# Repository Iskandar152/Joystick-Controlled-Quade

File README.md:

# Joystick-Controlled-Quade

## Project Goal

Creating a quadraped robot that uses an ultra sonic sensor and joystick to allow wireless control. The information from the ultra sonic sensor will allow the controller to guide the robot even if the controller cannot see where it is.

## MSP432 UART Connection

Based off [TI UART example code](http://dev.ti.com/tirex/explore/node?node=AHgBmlbzFK.HTw3HuKF7Cw__z-lQYNj__LATEST)
This example was chosen as the base because the baud rate was already set at 9600 which is necessary for communication with the Arduino Uno.

Altered to allow communication over the 3.2 and 3.3 pins on the MSP432 so that it can be connected to and Arduino Uno. It works with a receive interrupt that will then transmit the information from the ultra sonic sensor. 

## Arduino Blynk Code

Based off examples from the Blynk library, [Joystick Example](https://examples.blynk.cc/?board=Arduino%20Uno&shield=ESP8266%20WiFi%20Shield&example=Widgets%2FJoystickTwoAxis) and [Virtual Display](https://examples.blynk.cc/?board=Arduino%20Uno&shield=ESP8266%20WiFi%20Shield&example=GettingStarted%2FVirtualPinWrite).
Our code combines these examples and alters the display so that it is comstantly updating whenever new data is available.

This was an easy way to have a wireless connection with the MSP432 that just needed the addition of the UART communication to work with the TX and RX pins. The code creates an array for the joystick inputs and writes the sensor values to a digital display.

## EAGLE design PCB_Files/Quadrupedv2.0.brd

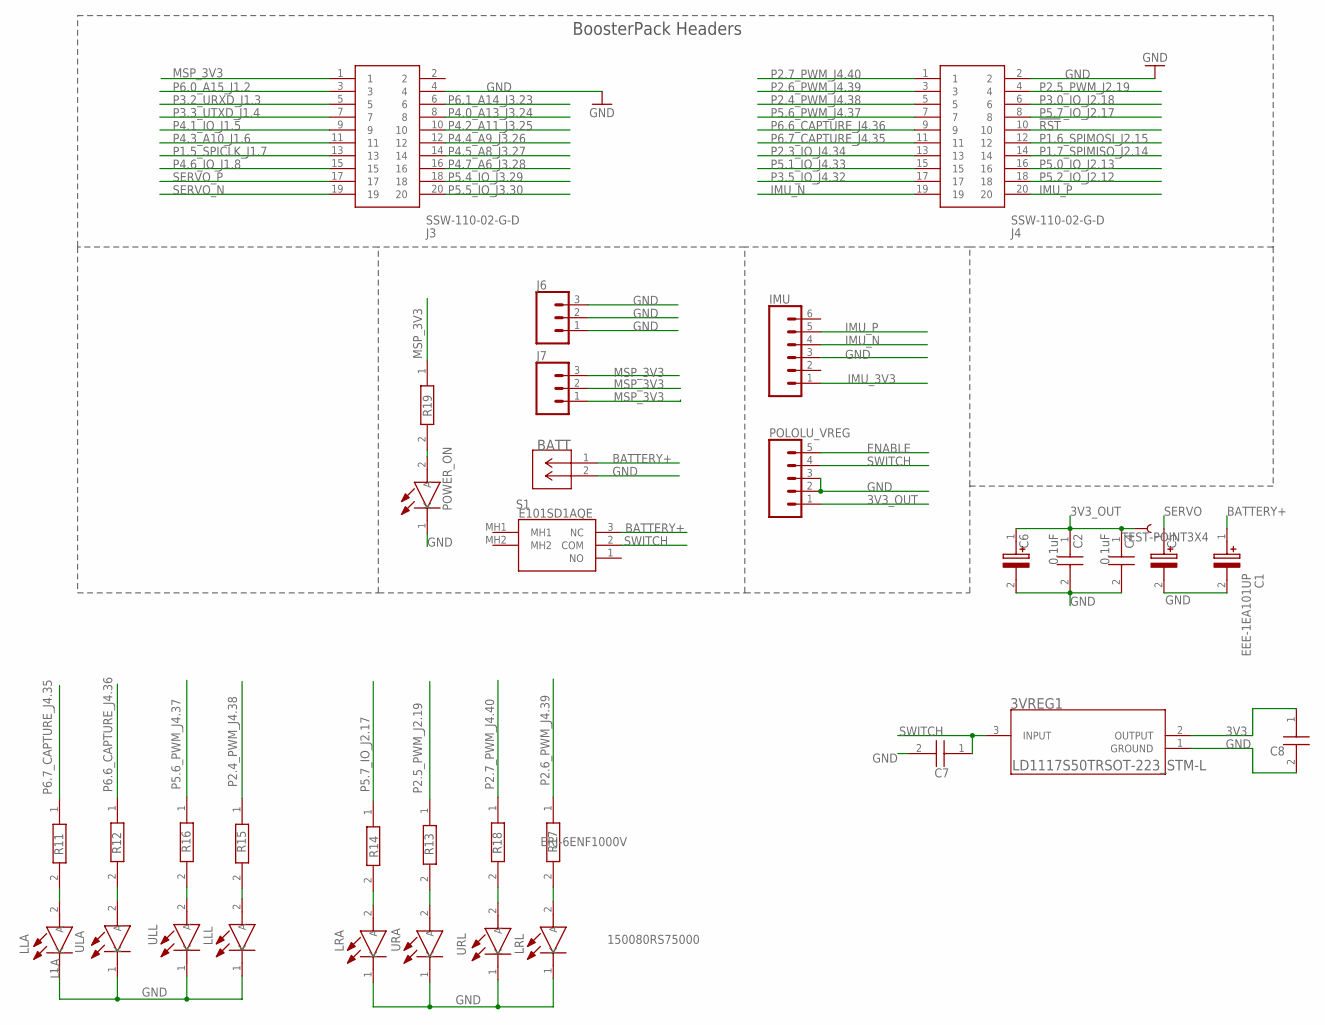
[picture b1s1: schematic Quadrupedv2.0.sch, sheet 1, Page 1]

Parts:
3VREG1: LD1117S50TRSOT-223_STM-L; SOT-223_STM-L
BATT: 640456-2; CONN2_640456-2_TEC
C1, C5, C6: EEE-1EA101UP; CAPAE830X650N
C2, C4: 0.1uF; CAPC2012X88N
C7, C8: C0805C104K5RAC7411; CAPC2012X88N
IMU: CONN_06SILK_FEMALE_PTH; 1X06
J3, J4: SSW-110-02-G-D; SAMTEC_SSW-110-02-G
J6, J7: CONN_03CONN_3F; 1X03_FEMALE
LLA: 150080RS75000; LEDC2012X80N
LLL: 150080RS75000; LEDC2012X80N
LRA: 150080RS75000; LEDC2012X80N
LRL: 150080RS75000; LEDC2012X80N
POLOLU_VREG: CONN_05; 1X05
POWER_ON: 150080RS75000; LEDC2012X80N
R11, R12, R13, R14, R15, R16, R17, R18, R19: ERJ-6ENF1000V; RESC2012X70N
S1: E101SD1AQE
TP22: TEST-POINT3X4; PAD.03X.04
ULA: 150080RS75000; LEDC2012X80N
ULL: 150080RS75000; LEDC2012X80N
URA: 150080RS75000; LEDC2012X80N
URL: 150080RS75000; LEDC2012X80N

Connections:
3V3: 3VREG1.2 (OUTPUT), C8.1; also elsewhere on the board
3V3_OUT: C2.1, C4.1, C6.1 (+), POLOLU_VREG.1, TP22.P$1; also elsewhere on the board
!RST: J4.10
BATTERY+: BATT.1, C1.1 (+), S1.3 (NC)
ENABLE: POLOLU_VREG.5
GND: 3VREG1.1 (GROUND), BATT.2, C1.2 (-), C2.2, C4.2, C5.2 (-), C6.2 (-), C7.2, C8.2, IMU.3, J3.4, J4.2, J6.1, J6.2, J6.3, LLA.1 (K), LLL.1 (K), LRA.1 (K), LRL.1 (K), POLOLU_VREG.2, POLOLU_VREG.3, POWER_ON.1 (K), ULA.1 (K), ULL.1 (K), URA.1 (K), URL.1 (K); also elsewhere on the board
IMU_3V3: IMU.1; also elsewhere on the board
IMU_N: IMU.4, J4.19
IMU_P: IMU.5, J4.20
MSP_3V3: J3.1, J7.1, J7.2, J7.3, R19.1; also elsewhere on the board
unnamed: R12.2, ULA.2 (A)
unnamed: LLA.2 (A), R11.2
unnamed: R16.2, ULL.2 (A)
unnamed: LLL.2 (A), R15.2
unnamed: R13.2, URA.2 (A)
unnamed: LRA.2 (A), R14.2
unnamed: R18.2, URL.2 (A)
unnamed: LRL.2 (A), R17.2
unnamed: POWER_ON.2 (A), R19.2
P1.5_SPICLK_J1.7: J3.13
P1.6_SPIMOSI_J2.15: J4.12
P1.7_SPIMISO_J2.14: J4.14
P2.3_IO_J4.34: J4.13
P2.4_PWM_J4.38: J4.5, R15.1
P2.5_PWM_J2.19: J4.4, R13.1
P2.6_PWM_J4.39: J4.3, R17.1
P2.7_PWM_J4.40: J4.1, R18.1
P3.0_IO_J2.18: J4.6
P3.2_URXD_J1.3: J3.5
P3.3_UTXD_J1.4: J3.7
P3.5_IO_J4.32: J4.17
P4.0_A13_J3.24: J3.8
P4.1_IO_J1.5: J3.9
P4.2_A11_J3.25: J3.10
P4.3_A10_J1.6: J3.11
P4.4_A9_J3.26: J3.12
P4.5_A8_J3.27: J3.14
P4.6_IO_J1.8: J3.15
P4.7_A6_J3.28: J3.16
P5.0_IO_J2.13: J4.16
P5.1_IO_J4.33: J4.15
P5.2_IO_J2.12: J4.18
P5.4_IO_J3.29: J3.18
P5.5_IO_J3.30: J3.20
P5.6_PWM_J4.37: J4.7, R16.1
P5.7_IO_J2.17: J4.8, R14.1
P6.0_A15_J1.2: J3.3
P6.1_A14_J3.23: J3.6
P6.6_CAPTURE_J4.36: J4.9, R12.1
P6.7_CAPTURE_J4.35: J4.11, R11.1
SERVO: C5.1 (+); also elsewhere on the board
SERVO_N: J3.19; also elsewhere on the board
SERVO_P: J3.17; also elsewhere on the board
SWITCH: 3VREG1.3 (INPUT), C7.1, POLOLU_VREG.4, S1.2 (COM)

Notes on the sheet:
BoosterPack Headers

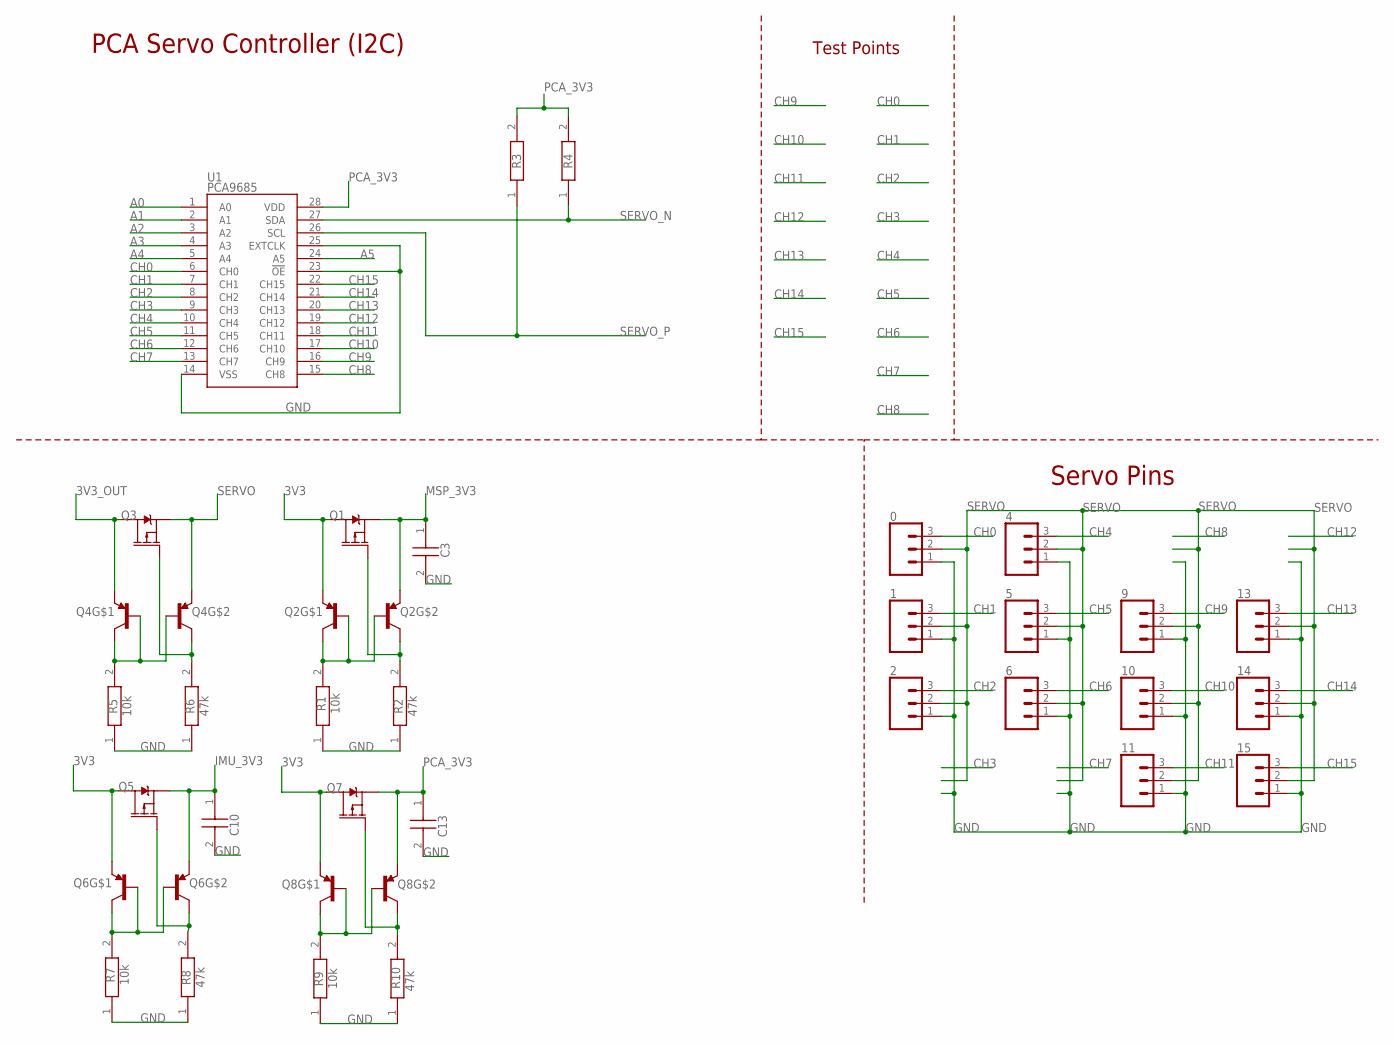
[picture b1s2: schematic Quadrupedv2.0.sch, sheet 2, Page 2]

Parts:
0, 1, 2, 4, 5, 6, 9, 10, 11, 13, 14, 15: CONN_03; 1X03MALE
C3, C10, C13: C0805C104K5RAC7411; CAPC2012X88N
Q1, Q3, Q5, Q7: 2.5A/30V/105mΩ; SOT23-3
Q2, Q4, Q6, Q8: TRANS_PNP_DUALSOT-363; SOT363_PHILIPS
R1, R5, R7, R9: 10k; RESC2012X70N
R2, R6, R8, R10: 47k; RESC2012X70N
R3, R4: ERJ-6ENF1000V; RESC2012X70N
U1: PCA9685; TSSOP-28_4MM

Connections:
3V3: Q1.3 (D), Q2.1 (E), Q5.3 (D), Q6.1 (E), Q7.3 (D), Q8.1 (E); also elsewhere on the board
3V3_OUT: Q3.3 (D), Q4.1 (E); also elsewhere on the board
A0: U1.1 (A0)
A1: U1.2 (A1)
A2: U1.3 (A2)
A3: U1.4 (A3)
A4: U1.5 (A4)
A5: U1.24 (A5)
CH0: 0.3, U1.6 (CH0)
CH1: 1.3, U1.7 (CH1)
CH2: 2.3, U1.8 (CH2)
CH3: U1.9 (CH3)
CH4: 4.3, U1.10 (CH4)
CH5: 5.3, U1.11 (CH5)
CH6: 6.3, U1.12 (CH6)
CH7: U1.13 (CH7)
CH8: U1.15 (CH8)
CH9: 9.3, U1.16 (CH9)
CH10: 10.3, U1.17 (CH10)
CH11: 11.3, U1.18 (CH11)
CH12: U1.19 (CH12)
CH13: 13.3, U1.20 (CH13)
CH14: 14.3, U1.21 (CH14)
CH15: 15.3, U1.22 (CH15)
GND: 0.1, 1.1, 2.1, 4.1, 5.1, 6.1, 9.1, 10.1, 11.1, 13.1, 14.1, 15.1, C3.2, C10.2, C13.2, R1.1, R2.1, R5.1, R6.1, R7.1, R8.1, R9.1, R10.1, U1.14 (VSS), U1.23 (!OE), U1.25 (EXTCLK); also elsewhere on the board
IMU_3V3: C10.1, Q5.2 (S), Q6.4 (E); also elsewhere on the board
MSP_3V3: C3.1, Q1.2 (S), Q2.4 (E); also elsewhere on the board
unnamed: Q7.1 (G), Q8.3 (C), R10.2
unnamed: Q8.2 (B), Q8.5 (B), Q8.6 (C), R9.2
unnamed: Q1.1 (G), Q2.3 (C), R2.2
unnamed: Q2.2 (B), Q2.5 (B), Q2.6 (C), R1.2
unnamed: Q5.1 (G), Q6.3 (C), R8.2
unnamed: Q6.2 (B), Q6.5 (B), Q6.6 (C), R7.2
unnamed: Q4.2 (B), Q4.5 (B), Q4.6 (C), R5.2
unnamed: Q3.1 (G), Q4.3 (C), R6.2
PCA_3V3: C13.1, Q7.2 (S), Q8.4 (E), R3.2, R4.2, U1.28 (VDD)
SERVO: 0.2, 1.2, 2.2, 4.2, 5.2, 6.2, 9.2, 10.2, 11.2, 13.2, 14.2, 15.2, Q3.2 (S), Q4.4 (E); also elsewhere on the board
SERVO_N: R4.1, U1.27 (SDA); also elsewhere on the board
SERVO_P: R3.1, U1.26 (SCL); also elsewhere on the board

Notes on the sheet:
PCA Servo Controller (I2C)
Test Points
Servo Pins

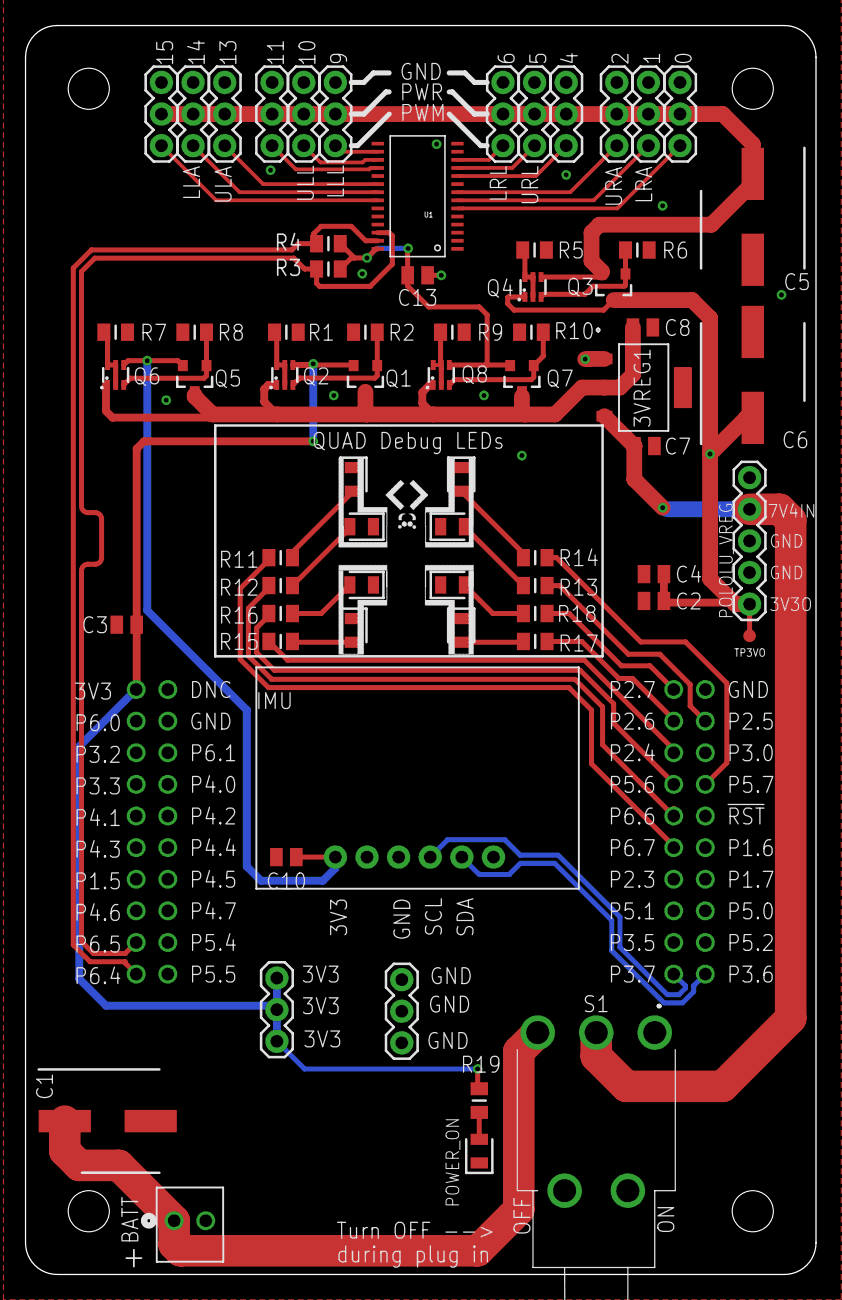
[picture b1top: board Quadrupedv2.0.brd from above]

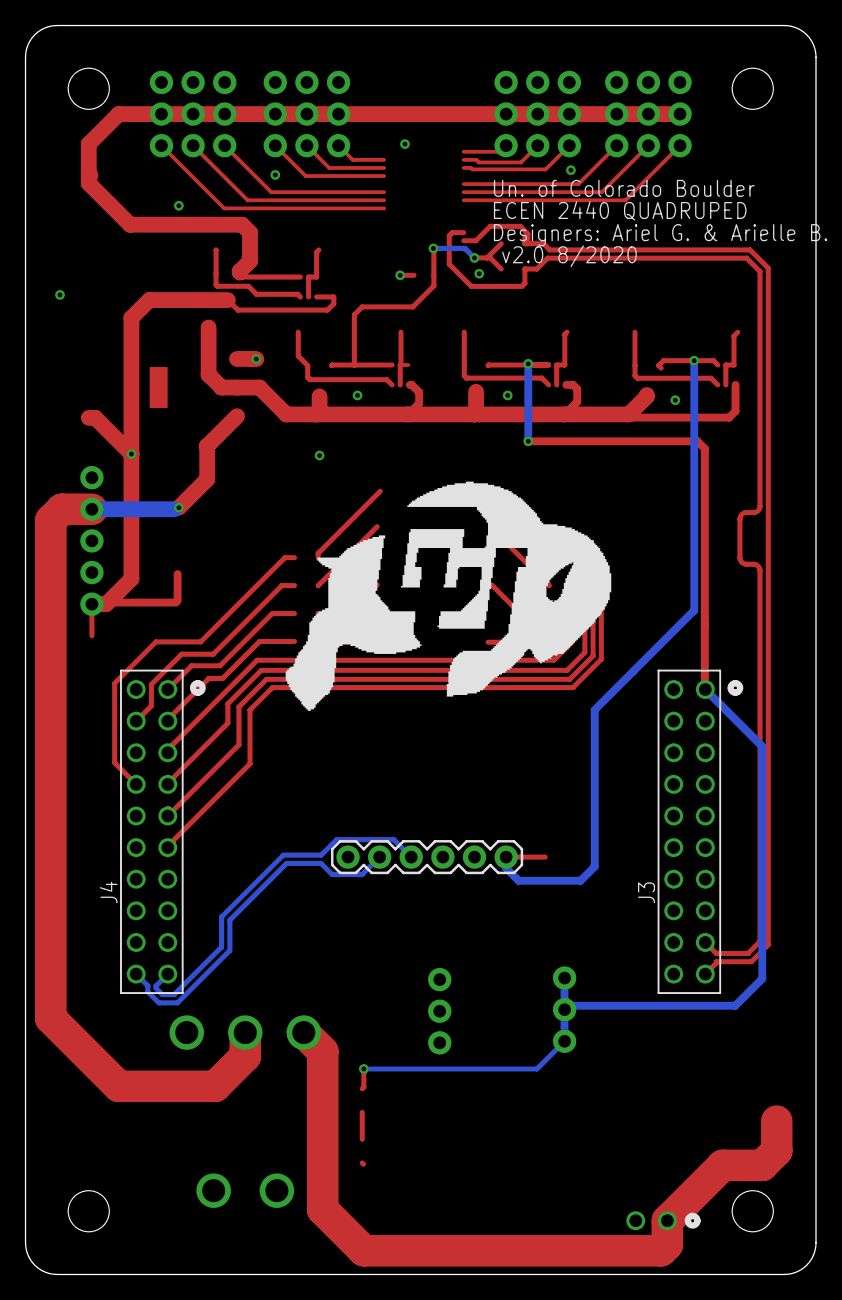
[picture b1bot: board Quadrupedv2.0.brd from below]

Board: 2 copper layers, 63.5 x 100.3 mm, 71 parts (4 on the bottom side), 50 nets.

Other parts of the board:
U$1: DEBUGLEDS
U$2: SKUBUFFS

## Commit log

2020-11-18 Add files via upload
    This code uses the Blynk code examples that are provided for a data push and joystick as a base.
2020-11-30 Create Wifi Arduino UART Communication
2020-11-30 Basic MSP432 UART communication
    Altered [TI UART example code](http://dev.ti.com/tirex/explore/node?node=AHgBmlbzFK.HTw3HuKF7Cw__z-lQYNj__LATEST)
2020-11-30 Code Information
2020-11-30 Rename README.MD to README.md

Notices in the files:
parts and their libraries:
SparkFun-DiscreteSemi: Licensing: Creative Commons ShareAlike 4.0 International - https://creativecommons.org/licenses/by-sa/4.0
COPYRIGHT: Copyright (C) 2016 Accelerated Designs. All rights reserved
